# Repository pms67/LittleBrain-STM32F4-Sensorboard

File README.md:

# LittleBrain-STM32F4-Sensorboard
STM32F4-based PCB interfacing with a variety of sensors.

- Learn how to design your own STM32-based PCB ([https://youtu.be/x_5rYfAyqq0](https://youtu.be/x_5rYfAyqq0))!
- Learn how to write firmware for the STM32 microcontroller ([https://youtu.be/C7-8nUU6e3E](https://youtu.be/C7-8nUU6e3E))!

You can order this board (incl. SMT assembly) at [https://www.jlcpcb.com/RPH](https://www.jlcpcb.com/RPH). Gerber and assembly files are in the relevant repo folders.

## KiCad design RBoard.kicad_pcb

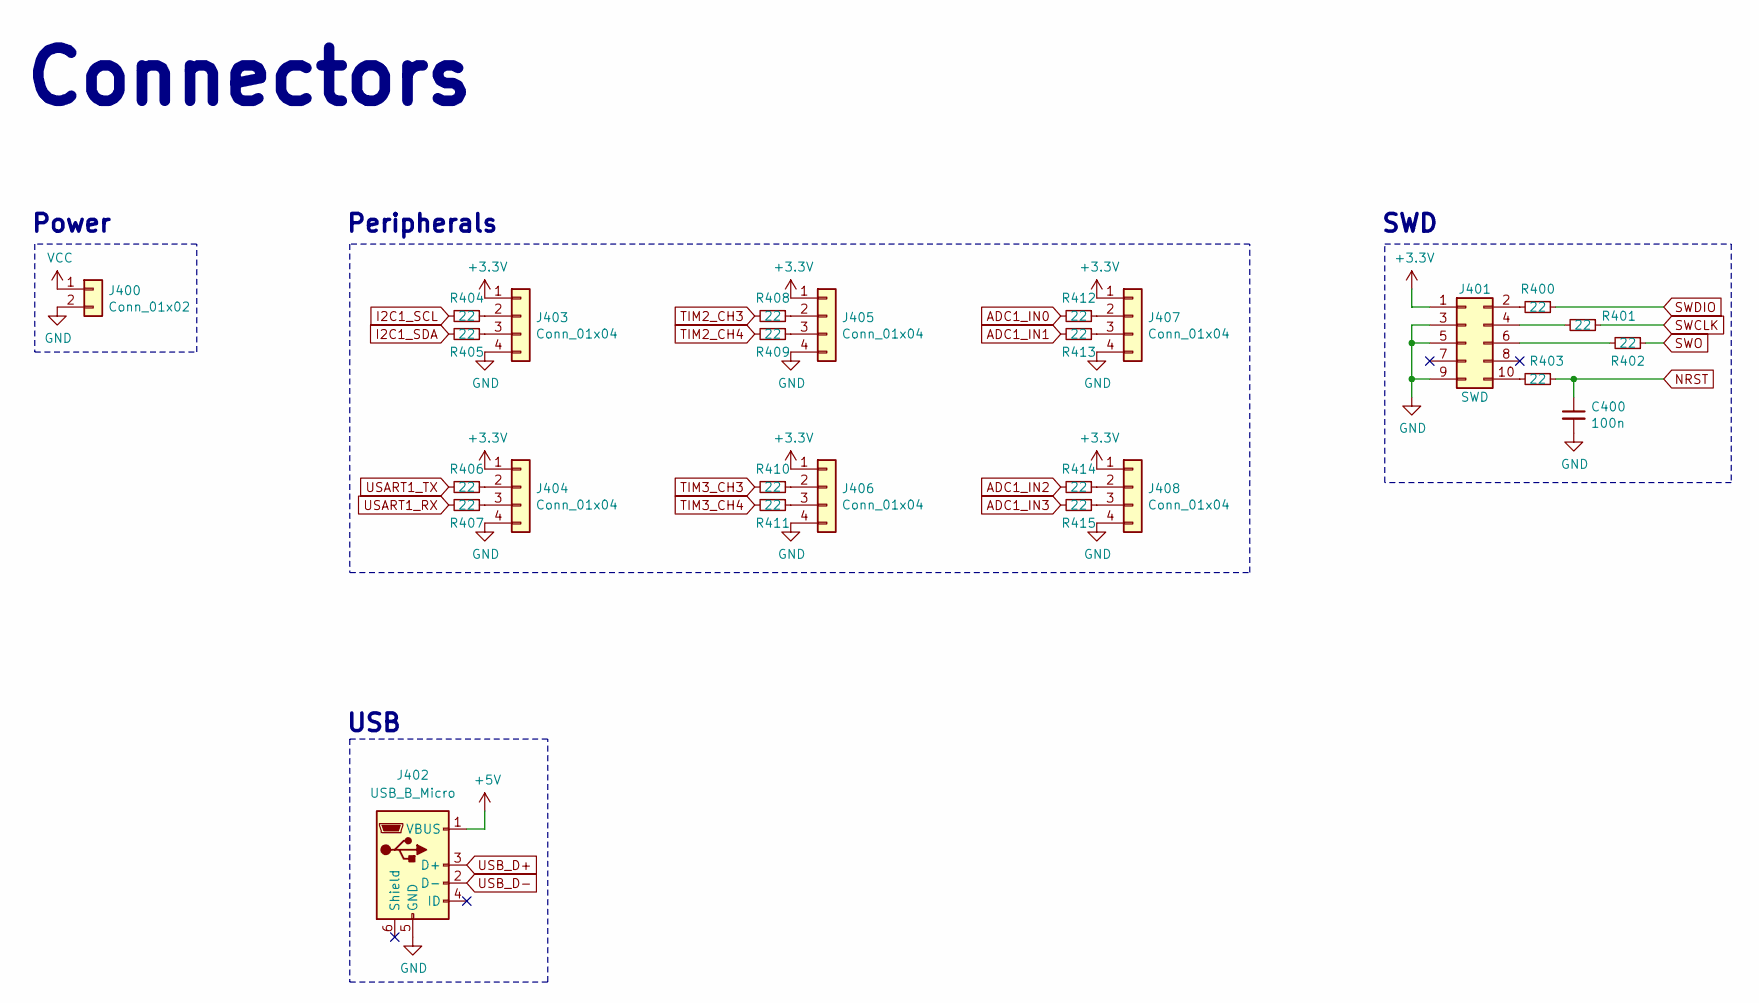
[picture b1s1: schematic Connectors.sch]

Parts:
C400: 100n; C_0402_1005Metric; LCSC Part # C1525
J400: Conn_01x02; Molex_PicoBlade_53048-0210_1x02_P1.25mm_Horizontal
J401: SWD; PinHeader_2x05_P1.27mm_Vertical_SMD
J402: USB_B_Micro; USB_Micro-B_Wuerth_629105150521
J403, J404, J405, J406, J407, J408: Conn_01x04; Molex_PicoBlade_53048-0410_1x04_P1.25mm_Horizontal
R400, R401, R402, R403, R404, R405, R406, R407, R408, R409, R410, R411, R412, R413, R414, R415: 22; R_0402_1005Metric; LCSC Part # C25092

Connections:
+3V3: J401.1, J403.1, J404.1, J405.1, J406.1, J407.1, J408.1; also elsewhere on the board
+5V: J402.1 (VBUS); also elsewhere on the board
ADC1_IN0: R412.2; also elsewhere on the board
ADC1_IN1: R413.2; also elsewhere on the board
ADC1_IN2: R414.2; also elsewhere on the board
ADC1_IN3: R415.2; also elsewhere on the board
GND: C400.2, J400.2, J401.3, J401.5, J401.9, J402.5 (GND), J403.4, J404.4, J405.4, J406.4, J407.4, J408.4; also elsewhere on the board
I2C1_SCL: R404.2; also elsewhere on the board
I2C1_SDA: R405.2; also elsewhere on the board
NRST: C400.1, R403.1; also elsewhere on the board
unnamed: J401.2, R400.2
unnamed: J401.4, R401.2
unnamed: J401.6, R402.2
unnamed: J401.10, R403.2
unnamed: J403.2, R404.1
unnamed: J403.3, R405.1
unnamed: J404.2, R406.1
unnamed: J404.3, R407.1
unnamed: J405.2, R408.1
unnamed: J405.3, R409.1
unnamed: J406.2, R410.1
unnamed: J406.3, R411.1
unnamed: J407.2, R412.1
unnamed: J407.3, R413.1
unnamed: J408.2, R414.1
unnamed: J408.3, R415.1
SWCLK: R401.1; also elsewhere on the board
SWDIO: R400.1; also elsewhere on the board
SWO: R402.1; also elsewhere on the board
TIM2_CH3: R408.2; also elsewhere on the board
TIM2_CH4: R409.2; also elsewhere on the board
TIM3_CH3: R410.2; also elsewhere on the board
TIM3_CH4: R411.2; also elsewhere on the board
USART1_RX: R407.2; also elsewhere on the board
USART1_TX: R406.2; also elsewhere on the board
USB_D+: J402.3 (D+); also elsewhere on the board
USB_D-: J402.2 (D-); also elsewhere on the board
VCC: J400.1; also elsewhere on the board

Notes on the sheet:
Connectors
USB
Peripherals
Power
SWD

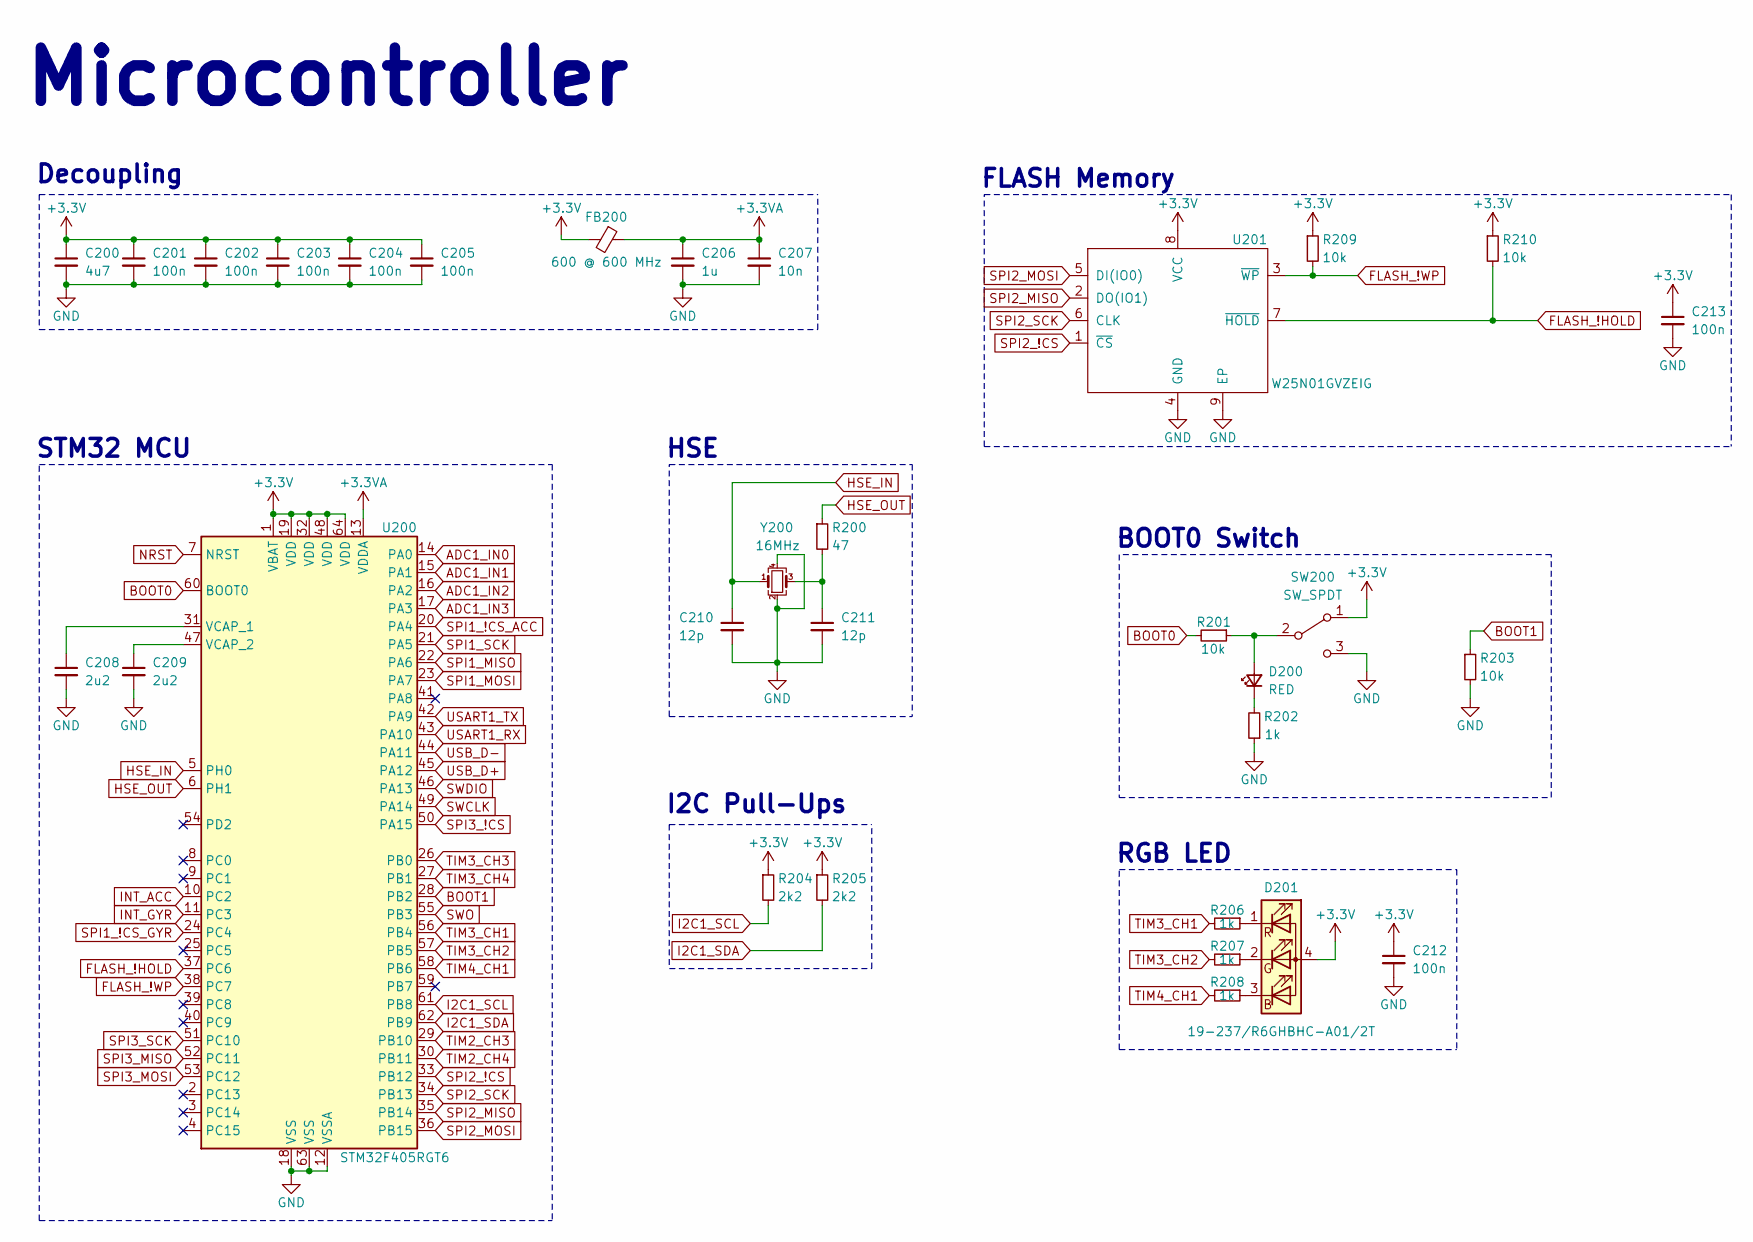
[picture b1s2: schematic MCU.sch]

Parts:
C200: 4u7; C_0603_1608Metric; LCSC Part # C19666
C201, C202, C203, C204, C205, C212, C213: 100n; C_0402_1005Metric; LCSC Part # C1525
C206: 1u; C_0402_1005Metric; LCSC Part # C52923
C207: 10n; C_0402_1005Metric; LCSC Part # C15195
C208, C209: 2u2; C_0603_1608Metric; LCSC Part # C23630
C210, C211: 12p; C_0402_1005Metric; LCSC Part # C1547
D200: RED; LED_0603_1608Metric; LCSC Part # C2286
D201: 19-237/R6GHBHC-A01/2T; 19-237-R6GHBHC-A01-2T; LCSC Part # C60105
FB200: 600 @ 600 MHz; L_0805_2012Metric; LCSC Part # C1017
R200: 47; R_0402_1005Metric; LCSC Part # C25118
R201, R203, R209, R210: 10k; R_0402_1005Metric; LCSC Part # C25744
R202: 1k; R_0603_1608Metric; LCSC Part # C21190
R204, R205: 2k2; R_0402_1005Metric; LCSC Part # C25879
R206, R207, R208: 1k; R_0402_1005Metric; LCSC Part # C11702
SW200: SW_SPDT; SW_SPDT_PCM12
U200: STM32F405RGT6; LQFP-64_10x10mm_P0.5mm; LCSC Part # C15742
U201: W25N01GVZEIG; LCSC Part # C88868
Y200: 16MHz; Crystal_SMD_3225-4Pin_3.2x2.5mm; LCSC Part # C13738

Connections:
+3.3VA: C206.1, C207.1, FB200.1, U200.13 (VDDA)
+3V3: C200.1, C201.1, C202.1, C203.1, C204.1, C205.1, C212.1, C213.1, D201.4 (A), FB200.2, R204.1, R205.1, R209.1, R210.1, SW200.1 (A), U200.1 (VBAT), U200.19 (VDD), U200.32 (VDD), U200.48 (VDD), U200.64 (VDD), U201.8 (VCC); also elsewhere on the board
ADC1_IN0: U200.14 (PA0); also elsewhere on the board
ADC1_IN1: U200.15 (PA1); also elsewhere on the board
ADC1_IN2: U200.16 (PA2); also elsewhere on the board
ADC1_IN3: U200.17 (PA3); also elsewhere on the board
BOOT0: R201.2, U200.60 (BOOT0)
BOOT1: R203.1, U200.28 (PB2)
FLASH_!HOLD: R210.2, U200.37 (PC6), U201.7 (~HOLD)
FLASH_!WP: R209.2, U200.38 (PC7), U201.3 (~WP)
GND: C200.2, C201.2, C202.2, C203.2, C204.2, C205.2, C206.2, C207.2, C208.2, C209.2, C210.2, C211.2, C212.2, C213.2, R202.1, R203.2, SW200.3 (C), U200.12 (VSSA), U200.18 (VSS), U200.63 (VSS), U201.4 (GND), U201.9 (EP), Y200.2, Y200.4; also elsewhere on the board
HSE_IN: C210.1, U200.5 (PH0), Y200.1
HSE_OUT: R200.1, U200.6 (PH1)
I2C1_SCL: R204.2, U200.61 (PB8); also elsewhere on the board
I2C1_SDA: R205.2, U200.62 (PB9); also elsewhere on the board
INT_ACC: U200.10 (PC2); also elsewhere on the board
INT_GYR: U200.11 (PC3); also elsewhere on the board
NRST: U200.7 (NRST); also elsewhere on the board
unnamed: C208.1, U200.31 (VCAP_1)
unnamed: C209.1, U200.47 (VCAP_2)
unnamed: C211.1, R200.2, Y200.3
unnamed: D200.1 (K), R202.2
unnamed: D200.2 (A), R201.1, SW200.2 (B)
unnamed: D201.1 (RK), R206.1
unnamed: D201.2 (GK), R207.1
unnamed: D201.3 (BK), R208.1
SPI1_!CS_ACC: U200.20 (PA4); also elsewhere on the board
SPI1_!CS_GYR: U200.24 (PC4); also elsewhere on the board
SPI1_MISO: U200.22 (PA6); also elsewhere on the board
SPI1_MOSI: U200.23 (PA7); also elsewhere on the board
SPI1_SCK: U200.21 (PA5); also elsewhere on the board
SPI2_!CS: U200.33 (PB12), U201.1 (~CS)
SPI2_MISO: U200.35 (PB14), U201.2 (DO(IO1))
SPI2_MOSI: U200.36 (PB15), U201.5 (DI(IO0))
SPI2_SCK: U200.34 (PB13), U201.6 (CLK)
SPI3_!CS: U200.50 (PA15); also elsewhere on the board
SPI3_MISO: U200.52 (PC11); also elsewhere on the board
SPI3_MOSI: U200.53 (PC12); also elsewhere on the board
SPI3_SCK: U200.51 (PC10); also elsewhere on the board
SWCLK: U200.49 (PA14); also elsewhere on the board
SWDIO: U200.46 (PA13); also elsewhere on the board
SWO: U200.55 (PB3); also elsewhere on the board
TIM2_CH3: U200.29 (PB10); also elsewhere on the board
TIM2_CH4: U200.30 (PB11); also elsewhere on the board
TIM3_CH1: R206.2, U200.56 (PB4)
TIM3_CH2: R207.2, U200.57 (PB5)
TIM3_CH3: U200.26 (PB0); also elsewhere on the board
TIM3_CH4: U200.27 (PB1); also elsewhere on the board
TIM4_CH1: R208.2, U200.58 (PB6)
USART1_RX: U200.43 (PA10); also elsewhere on the board
USART1_TX: U200.42 (PA9); also elsewhere on the board
USB_D+: U200.45 (PA12); also elsewhere on the board
USB_D-: U200.44 (PA11); also elsewhere on the board

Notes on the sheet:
Microcontroller
STM32 MCU
Decoupling
HSE
FLASH Memory
BOOT0 Switch
RGB LED
I2C Pull-Ups

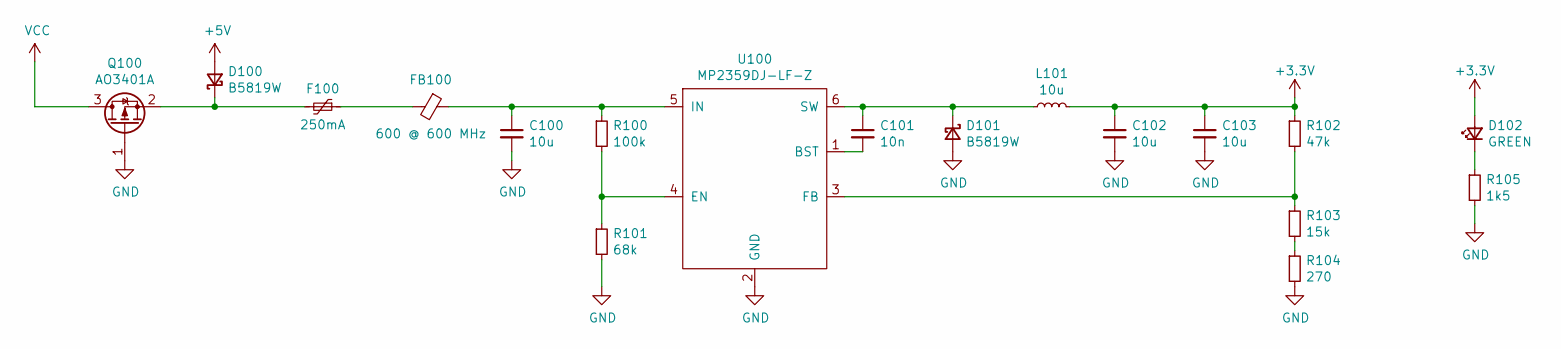
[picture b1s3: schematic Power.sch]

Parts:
C100, C102, C103: 10u; C_1206_3216Metric; LCSC Part # C13585
C101: 10n; C_0603_1608Metric; LCSC Part # C57112
D100, D101: B5819W; D_SOD-123; LCSC Part # C8598
D102: GREEN; LED_0603_1608Metric; LCSC Part # C72043
F100: 250mA; Fuse_1206_3216Metric; LCSC Part # C70068
FB100: 600 @ 600 MHz; L_0805_2012Metric; LCSC Part # C1017
L101: 10u; L_Sunlord_MWSA0518_5.4x5.2mm; LCSC Part # C139506
Q100: AO3401A; SOT-23; LCSC Part # C15127
R100: 100k; R_0603_1608Metric; LCSC Part # C25803
R101: 68k; R_0603_1608Metric; LCSC Part # C23231
R102: 47k; R_0603_1608Metric; LCSC Part # C25819
R103: 15k; R_0603_1608Metric; LCSC Part # C22809
R104: 270; R_0603_1608Metric; LCSC Part # C22966
R105: 1k5; R_0603_1608Metric; LCSC Part # C22843
U100: MP2359DJ-LF-Z; SOT-23-6; LCSC Part # C14259

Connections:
+3V3: C102.1, C103.1, D102.2 (A), L101.2, R102.1; also elsewhere on the board
+5V: D100.2 (A); also elsewhere on the board
GND: C100.2, C102.2, C103.2, D101.2 (A), Q100.1 (G), R101.2, R104.2, R105.2, U100.2 (GND); also elsewhere on the board
unnamed: C100.1, FB100.1, R100.1, U100.5 (IN)
unnamed: C101.1, D101.1 (K), L101.1, U100.6 (SW)
unnamed: C101.2, U100.1 (BST)
unnamed: D100.1 (K), F100.2, Q100.2 (S)
unnamed: D102.1 (K), R105.1
unnamed: F100.1, FB100.2
unnamed: R100.2, R101.1, U100.4 (EN)
unnamed: R102.2, R103.1, U100.3 (FB)
unnamed: R103.2, R104.1
VCC: Q100.3 (D); also elsewhere on the board

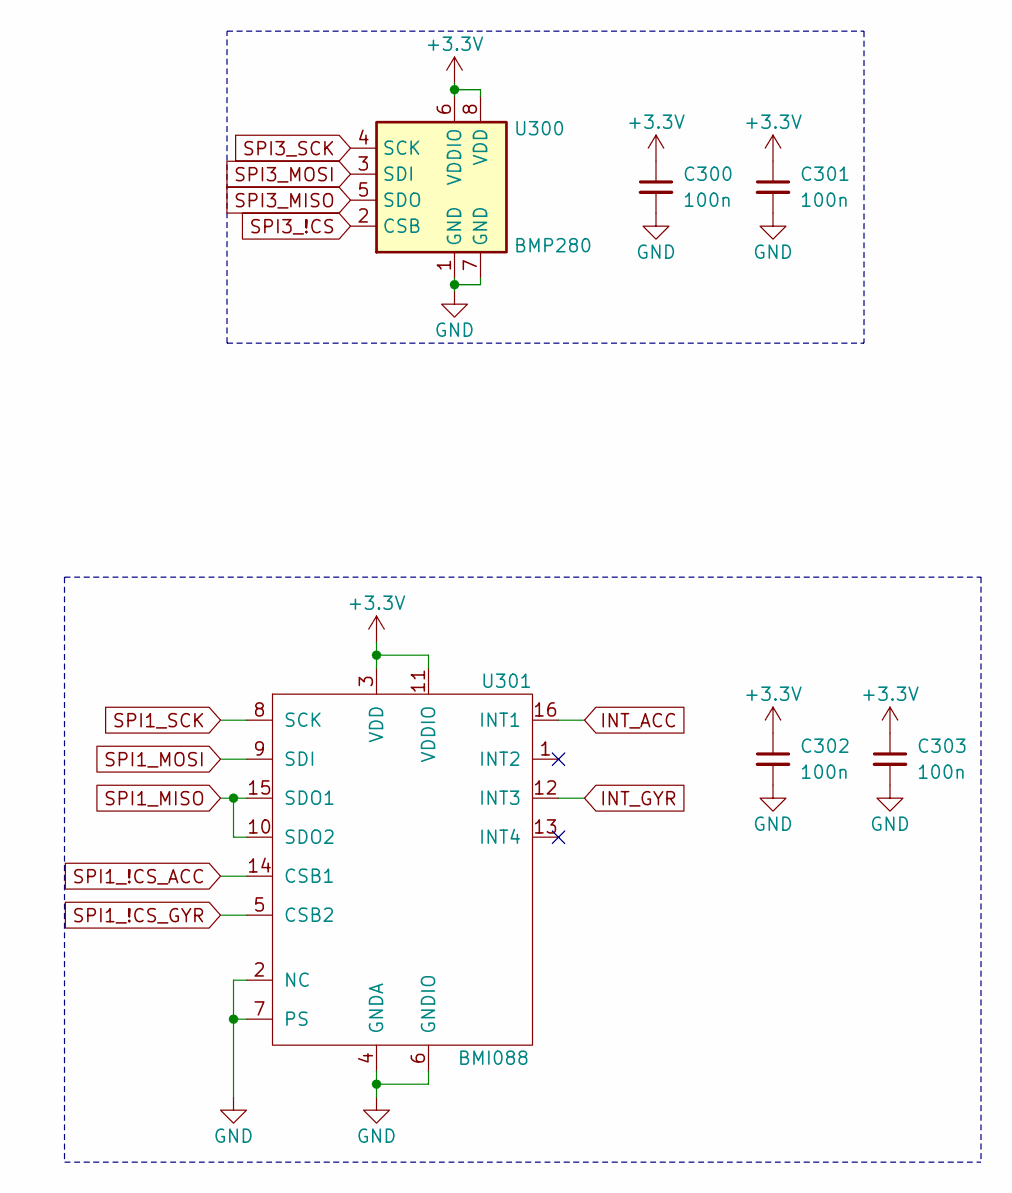
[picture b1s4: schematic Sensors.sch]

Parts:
C300, C301, C302, C303: 100n; C_0402_1005Metric; LCSC Part # C1525
U300: BMP280; Bosch_LGA-8_2x2.5mm_P0.65mm_ClockwisePinNumbering; LCSC Part # C233787
U301: BMI088; LCSC Part # C194919

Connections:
+3V3: C300.1, C301.1, C302.1, C303.1, U300.6 (VDDIO), U300.8 (VDD), U301.3 (VDD), U301.11 (VDDIO); also elsewhere on the board
GND: C300.2, C301.2, C302.2, C303.2, U300.1 (GND), U300.7 (GND), U301.2 (NC), U301.4 (GNDA), U301.6 (GNDIO), U301.7 (PS); also elsewhere on the board
INT_ACC: U301.16 (INT1); also elsewhere on the board
INT_GYR: U301.12 (INT3); also elsewhere on the board
SPI1_!CS_ACC: U301.14 (CSB1); also elsewhere on the board
SPI1_!CS_GYR: U301.5 (CSB2); also elsewhere on the board
SPI1_MISO: U301.10 (SDO2), U301.15 (SDO1); also elsewhere on the board
SPI1_MOSI: U301.9 (SDI); also elsewhere on the board
SPI1_SCK: U301.8 (SCK); also elsewhere on the board
SPI3_!CS: U300.2 (CSB); also elsewhere on the board
SPI3_MISO: U300.5 (SDO); also elsewhere on the board
SPI3_MOSI: U300.3 (SDI); also elsewhere on the board
SPI3_SCK: U300.4 (SCK); also elsewhere on the board

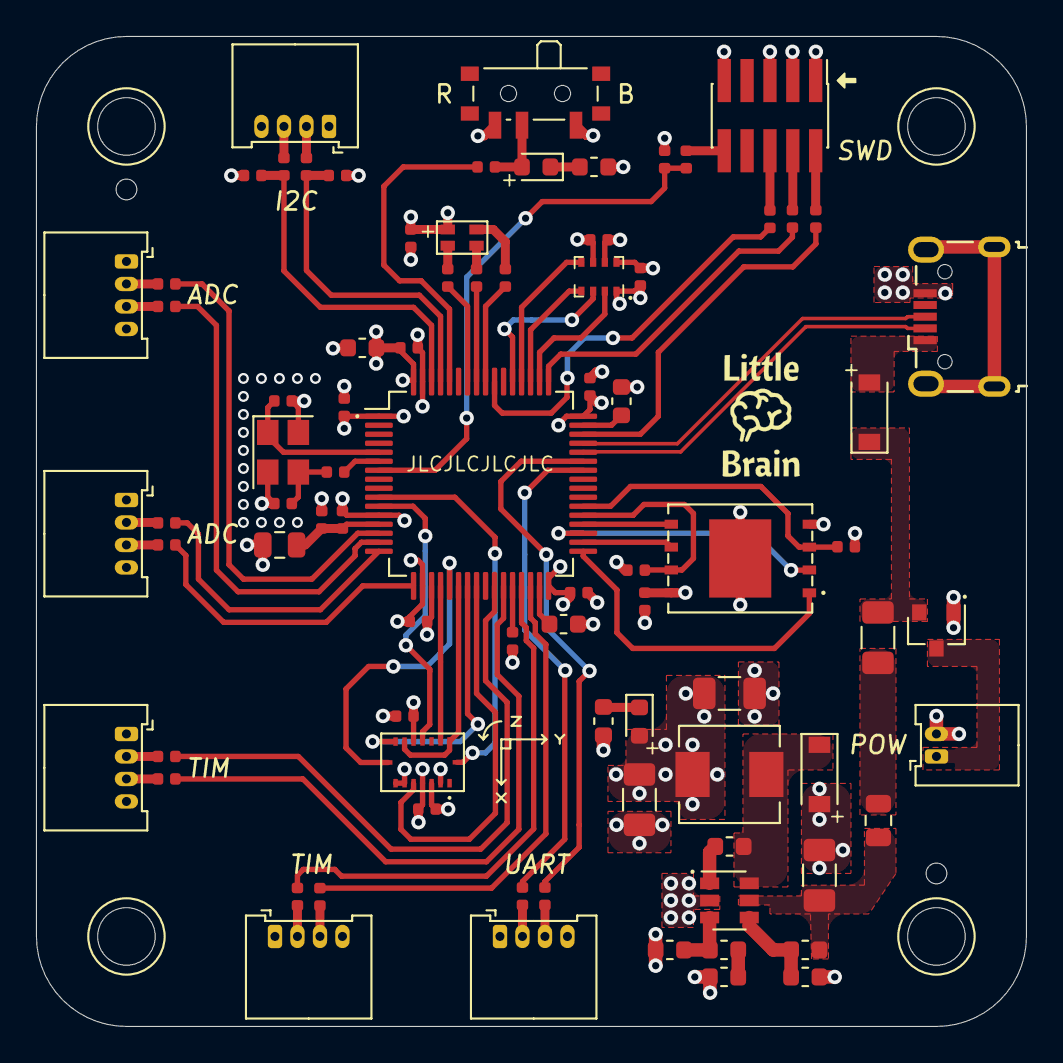
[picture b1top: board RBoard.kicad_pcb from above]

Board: 4 copper layers, 55.0 x 55.0 mm, 86 parts (0 on the bottom side), 80 nets.

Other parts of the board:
H1, H2, H3, H4: MountingHole; MountingHole_3.2mm_M3

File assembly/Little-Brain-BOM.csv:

Comment,Designator,Footprint,LCSC
"10u","C100,C102,C103","Capacitor_SMD:C_1206_3216Metric","C13585"
"10n","C101","Capacitor_SMD:C_0603_1608Metric","C57112"
"4u7","C200","Capacitor_SMD:C_0603_1608Metric","C19666"
"1u","C206","Capacitor_SMD:C_0402_1005Metric","C52923"
"10n","C207","Capacitor_SMD:C_0402_1005Metric","C15195"
"2u2","C208,C209","Capacitor_SMD:C_0603_1608Metric","C23630"
"12p","C210,C211","Capacitor_SMD:C_0402_1005Metric","C1547"
"100n","C201,C202,C203,C204,C205,C212,C213,C300,C301,C302,C303,C400","Capacitor_SMD:C_0402_1005Metric","C1525"
"B5819W","D100,D101","Diode_SMD:D_SOD-123","C8598"
"GREEN","D102","LED_SMD:LED_0603_1608Metric","C72043"
"RED","D200","LED_SMD:LED_0603_1608Metric","C2286"
"19-237/R6GHBHC-A01/2T","D201","RGB_LED:19-237-R6GHBHC-A01-2T","C60105"
"250mA","F100","Fuse:Fuse_1206_3216Metric","C70068"
"600 @ 600 MHz","FB100,FB200","Inductor_SMD:L_0805_2012Metric","C1017"
"10u","L101","Inductor_SMD:L_Sunlord_MWSA0518_5.4x5.2mm","C139506"
"AO3401A","Q100","Package_TO_SOT_SMD:SOT-23","C15127"
"100k","R100","Resistor_SMD:R_0603_1608Metric","C25803"
"68k","R101","Resistor_SMD:R_0603_1608Metric","C23231"
"47k","R102","Resistor_SMD:R_0603_1608Metric","C25819"
"15k","R103","Resistor_SMD:R_0603_1608Metric","C22809"
"270","R104","Resistor_SMD:R_0603_1608Metric","C22966"
"1k5","R105","Resistor_SMD:R_0603_1608Metric","C22843"
"47","R200","Resistor_SMD:R_0402_1005Metric","C25118"
"1k","R202","Resistor_SMD:R_0603_1608Metric","C21190"
"2k2","R204,R205","Resistor_SMD:R_0402_1005Metric","C25879"
"1k","R206,R207,R208","Resistor_SMD:R_0402_1005Metric","C11702"
"10k","R201,R203,R209,R210","Resistor_SMD:R_0402_1005Metric","C25744"
"22","R400,R401,R402,R403,R404,R405,R406,R407,R408,R409,R410,R411,R412,R413,R414,R415","Resistor_SMD:R_0402_1005Metric","C25092"
"MP2359DJ-LF-Z","U100","Package_TO_SOT_SMD:SOT-23-6","C14259"
"STM32F405RGT6","U200","Package_QFP:LQFP-64_10x10mm_P0.5mm","C15742"
"W25N01GVZEIG","U201","WinbondFlash:W25N01GVZEIG","C88868"
"BMP280","U300","Package_LGA:Bosch_LGA-8_2x2.5mm_P0.65mm_ClockwisePinNumbering","C233787"
"BMI088","U301","BMI088:BMI088","C194919"
"16MHz","Y200","Crystal:Crystal_SMD_3225-4Pin_3.2x2.5mm","C13738"

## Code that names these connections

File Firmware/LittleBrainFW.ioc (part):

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Mcu.Name=STM32F405RGTx
Mcu.Package=LQFP64
Mcu.UserName=STM32F405RGTx
PA11.Mode=Device_Only
PA11.Signal=USB_OTG_FS_DM
PA12.Mode=Device_Only
PA12.Signal=USB_OTG_FS_DP
PA13.Mode=Trace_Asynchronous_SW
PA13.Signal=SYS_JTMS-SWDIO
PA14.Mode=Trace_Asynchronous_SW
PA14.Signal=SYS_JTCK-SWCLK
PA15.GPIOParameters=GPIO_Label
PA15.GPIO_Label=SPI3_NCS
PA15.Signal=GPIO_Output
PA4.GPIOParameters=GPIO_Label
PA4.GPIO_Label=SPI1_NCS_ACC
PA4.Signal=GPIO_Output
PA5.Mode=Full_Duplex_Master
PA5.Signal=SPI1_SCK
PA6.Mode=Full_Duplex_Master
PA6.Signal=SPI1_MISO
PA7.Mode=Full_Duplex_Master
PA7.Signal=SPI1_MOSI
PB3.Mode=Trace_Asynchronous_SW
PB3.Signal=SYS_JTDO-SWO
PB4.GPIOParameters=GPIO_Label
PB4.GPIO_Label=LED_RED
PB4.Signal=S_TIM3_CH1
PB5.GPIOParameters=GPIO_Label
PB5.GPIO_Label=LED_GREEN
PB5.Signal=S_TIM3_CH2
PB6.GPIOParameters=GPIO_Label
PB6.GPIO_Label=LED_BLUE
PB6.Signal=S_TIM4_CH1
PC10.Mode=Full_Duplex_Master
PC10.Signal=SPI3_SCK
PC11.Mode=Full_Duplex_Master
PC11.Signal=SPI3_MISO
PC12.Mode=Full_Duplex_Master
PC12.Signal=SPI3_MOSI
PC2.GPIOParameters=GPIO_Label
PC2.GPIO_Label=INT_ACC
PC2.Signal=GPXTI2
PC3.GPIOParameters=GPIO_Label
PC3.GPIO_Label=INT_GYR
PC3.Signal=GPXTI3
PC4.GPIOParameters=GPIO_Label
PC4.GPIO_Label=SPI1_NCS_GYR
PC4.Signal=GPIO_Output
PC6.GPIOParameters=GPIO_Label
PC6.GPIO_Label=FLASH_NHOLD
PC6.Signal=GPIO_Output
PC7.GPIOParameters=GPIO_Label
PC7.GPIO_Label=FLASH_NWP
PC7.Signal=GPIO_Output
PH0-OSC_IN.Mode=HSE-External-Oscillator
PH0-OSC_IN.Signal=RCC_OSC_IN
PH1-OSC_OUT.Mode=HSE-External-Oscillator
PH1-OSC_OUT.Signal=RCC_OSC_OUT
RCC.HSE_VALUE=16000000
RCC.SYSCLKFreq_VALUE=168000000
RCC.SYSCLKSource=RCC_SYSCLKSOURCE_PLLCLK
board=custom

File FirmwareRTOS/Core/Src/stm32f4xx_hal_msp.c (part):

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
    __HAL_RCC_GPIOA_CLK_ENABLE();
    /**SPI1 GPIO Configuration
    PA5     ------> SPI1_SCK
    PA6     ------> SPI1_MISO
    PA7     ------> SPI1_MOSI
    */
    GPIO_InitStruct.Pin = GPIO_PIN_5|GPIO_PIN_6|GPIO_PIN_7;
    GPIO_InitStruct.Mode = GPIO_MODE_AF_PP;
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
    __HAL_RCC_GPIOC_CLK_ENABLE();
    /**SPI3 GPIO Configuration
    PC10     ------> SPI3_SCK
    PC11     ------> SPI3_MISO
    PC12     ------> SPI3_MOSI
    */
    GPIO_InitStruct.Pin = GPIO_PIN_10|GPIO_PIN_11|GPIO_PIN_12;
    GPIO_InitStruct.Mode = GPIO_MODE_AF_PP;
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    __HAL_RCC_SPI1_CLK_DISABLE();

    /**SPI1 GPIO Configuration
    PA5     ------> SPI1_SCK
    PA6     ------> SPI1_MISO
    PA7     ------> SPI1_MOSI
    */
    HAL_GPIO_DeInit(GPIOA, GPIO_PIN_5|GPIO_PIN_6|GPIO_PIN_7);

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    __HAL_RCC_SPI3_CLK_DISABLE();

    /**SPI3 GPIO Configuration
    PC10     ------> SPI3_SCK
    PC11     ------> SPI3_MISO
    PC12     ------> SPI3_MOSI
    */
    HAL_GPIO_DeInit(GPIOC, GPIO_PIN_10|GPIO_PIN_11|GPIO_PIN_12);

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  /* USER CODE END TIM3_MspPostInit 0 */
    __HAL_RCC_GPIOB_CLK_ENABLE();
    /**TIM3 GPIO Configuration
    PB4     ------> TIM3_CH1
    PB5     ------> TIM3_CH2
    */
    GPIO_InitStruct.Pin = LED_RED_Pin|LED_GREEN_Pin;
    GPIO_InitStruct.Mode = GPIO_MODE_AF_PP;
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
    __HAL_RCC_GPIOB_CLK_ENABLE();
    /**TIM4 GPIO Configuration
    PB6     ------> TIM4_CH1
    */
    GPIO_InitStruct.Pin = LED_BLUE_Pin;
    GPIO_InitStruct.Mode = GPIO_MODE_AF_PP;
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
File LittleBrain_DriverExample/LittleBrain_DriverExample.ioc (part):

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Mcu.Name=STM32F405RGTx
Mcu.Package=LQFP64
Mcu.UserName=STM32F405RGTx
PA1.GPIOParameters=GPIO_Label
PA1.GPIO_Label=ACC_INT
PA1.Signal=GPXTI1
PA11.Mode=Device_Only
PA11.Signal=USB_OTG_FS_DM
PA12.Mode=Device_Only
PA12.Signal=USB_OTG_FS_DP
PA13.Mode=Trace_Asynchronous_SW
PA13.Signal=SYS_JTMS-SWDIO
PA14.Mode=Trace_Asynchronous_SW
PA14.Signal=SYS_JTCK-SWCLK
PB3.Mode=Trace_Asynchronous_SW
PB3.Signal=SYS_JTDO-SWO
PB4.GPIOParameters=GPIO_Label
PB4.GPIO_Label=LED
PB4.Signal=GPIO_Output
PB8.Mode=I2C
PB8.Signal=I2C1_SCL
PB9.Mode=I2C
PB9.Signal=I2C1_SDA
PH0-OSC_IN.Mode=HSE-External-Oscillator
PH0-OSC_IN.Signal=RCC_OSC_IN
PH1-OSC_OUT.Mode=HSE-External-Oscillator
PH1-OSC_OUT.Signal=RCC_OSC_OUT
RCC.HSE_VALUE=16000000
RCC.SYSCLKFreq_VALUE=168000000
RCC.SYSCLKSource=RCC_SYSCLKSOURCE_PLLCLK
board=custom

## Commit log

2020-10-24 Initial commit.
2020-10-25 Updated firmware. Added schematic PDF.
2020-10-25 DMA for SPI (BMI088).
2020-10-25 SPL06 pressure sensor driver.
2020-10-25 DMA for pressure sensor.
2020-11-07 FreeRTOS implementation.
2020-11-08 Fixed bug, made DMA txBuf persistent.
2020-11-08 FreeRTOS DMA.
2020-11-11 Changed USB connector.
2020-12-20 Added FIR filtering routines.
2021-09-11 Various filters (IIR), ADXL355 driver.

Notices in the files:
FirmwareRTOS/Core/Src/stm32f4xx_hal_msp.c:
© Copyright (c) 2020 STMicroelectronics.
All rights reserved.
This software component is licensed by ST under Ultimate Liberty license
(C) COPYRIGHT STMicroelectronics *****END OF FILE
